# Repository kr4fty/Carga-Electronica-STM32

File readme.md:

# CARGA ELECTRÓNICA FANTASMA

La carga electrónica fantasma es un dispositivo diseñado para simular una carga eléctrica, utilizado principalmente para pruebas y mediciones. 

Este proyecto está basado en un microcontrolador STM32F103, el cual controla la Vgs del MOSFET para regular la corriente.

**Estado del proyecto:** Funcional, pero aún en proceso de creación.

----------------- **BAJO SU RESPONSABILIDAD** ----------------------

### Video

[Demo](https://github.com/user-attachments/assets/e986f7fb-c2cd-4f63-a5ff-34d32783e475)

## Preparación Previa

Dado que cada transistor MOSFET presenta un voltaje umbral de puerta a fuente (Vgs Threshold) único, independientemente del fabricante o del código de identificación, es imperativo llevar a cabo mediciones específicas para determinar este voltaje umbral, así como la relación entre el ciclo de trabajo (Duty Cycle) y la corriente.

Para ello, se empleará el proyecto [Data Logger](https://github.com/kr4fty/DataLogger_STM32) con el fin de registrar estos parámetros. Posteriormente, los valores obtenidos se integrarán en este proyecto para facilitar el control adecuado de nuestra carga electrónica.

## Que incluye este repositorio?

Actualmente este repositorio cuenta con:
 - Diseño del hardware necesario para el proyecto
 - Codigo fuentes, tanto el de Control como la de adquicision de Datos
 - Archivo necesario para simular la placa BluePill, mediante PICSIMLAB

## Materiales

- **Placa:** BLUE PILL (STM32F103)
- **Encoder con botón**
- **Pantalla LCD:** Nokia 5110
- **Buzzer**
- **Sensor de temperatura:** LM35
- **Cooler Fan**
- **Transistor/s MOSFET:** IRFZ44
- **Sensor de corriente:** ACS712-05B

## Principio de Funcionamiento

El MOSFET opera en la zona de saturación (o zona lineal), lo que permite mantener una corriente constante independientemente de la tensión Vds de entrada. Esta característica es ventajosa para nuestra aplicación, ya que al variar la tensión Vgs podemos ajustar la corriente de salida de manera precisa.

La tensión Vds será controlada mediante el STM32F103 utilizando modulación por ancho de pulso (PWM) y un filtro pasa-bajos para obtener una señal de conversión digital a analógica (DAC) de 12 bits.

Debido a la inestabilidad de la potencia con respecto a la temperatura de los mosfset, el lazo de control sera realizado mediante un PID, el cual debera tener en cuenta el rango de temperaturas no solo para mantener la corriente constante, si no tambien para mantener a salvo al dispositivo.

#### Consideraciones importantes de los transistores Mosfet

- **Tensión de umbral (Vgs threshold):** Es el voltaje mínimo que debe aplicarse entre la puerta y la fuente para que el MOSFET comience a conducir corriente entre el drenador y la fuente.
- **Disipación de potencia:** Operar en la zona de saturación genera una significativa disipación de potencia en el MOSFET. Por lo tanto, es necesario implementar un sistema de disipación forzada para evitar el sobrecalentamiento.

#### Modos de Operacion
* Modo de **Corriente Constante**: Este es el modo predeterminado de operación, en el cual el dispositivo mantiene un nivel de corriente constante, determinado por el operador. Este modo es ideal para evaluar el comportamiento de una fuente o batería al operar bajo una corriente estable.
* Modo de **Potencia Constante**: En este modo, el dispositivo ajusta automáticamente la corriente para mantener la potencia consumida constante en la carga. Este enfoque es útil en situaciones donde es crítico mantener un nivel de potencia específico.
* Modo de **Tiempo**: Este modo permite al operador establecer un intervalo de tiempo durante el cual la carga permanecerá activa. Se pueden utilizar cualquiera de los modos anteriores en conjunto con este, según las necesidades de la aplicación.

## Modo de Funcionamiento

 * Al encender el equipo:
  El sistema muestra una pantalla con los siguientes parámetros:
    * **Tensión mínima (Vmin Limite):** 0.00 V (por defecto).
    * **Corriente de carga:** 1.00 A (por defecto).
    * **Modo de Operación:** "Corriente Constante" (por defecto).

 * Modificación de parámetros:
    * **Selección de parámetros:** Gira el encoder para resaltar el parámetro deseado (se invertirán los colores en el seleccionado).
    * **Edición de parámetros:** Realiza un giro rápido hacia la izquierda para entrar en modo edición. El parámetro comenzará a parpadear.
    * **Ajuste de valores:** Gira el encoder para incrementar o decrementar el valor.
    * **Confirmación:** Espera 2 segundos para salir del modo edición.

* Inicio del proceso:
    * **Inicio:** Haz un click corto en el botón para comenzar el proceso.
    * **Parada:** Un click corto detendrá el proceso.

* Modificación de parámetros estando el proceso en funcionamiento:
    - Puedes editar los parámetros de la misma manera que en el estado inicial de arranque (selección y edición).

* Menú:
    * **Acceso al menú:** Haz un doble click en el botón.

    * **Opciones del menú:**
        * Configurar
            * Backlight.
        * Modo de Trabajo
            * Corriente Cte.
            * Potencia Cte.
            * Resistencia Cte.
            * Tiempo Limite
            * Prueba de carga
            * Reset modo actual
        * Set Vmin Limite
        * Calibración
            * Calibrar
            * Ver parámetros
            * Borrar parámetros
        * Reiniciar MCU
        * Salir del Menú

## Hardware

El diseño del hardware se realizó utilizando KiCad, y se ha optimizado para facilitar la conexión de todos los componentes. A continuación, se detallan los aspectos clave del diseño:

### Consideraciones de Diseño

- **Disipación de Calor:** Asegúrate de que el MOSFET esté montado en un disipador de calor adecuado para evitar el sobrecalentamiento durante su operación.
- **Conexiones Seguras:** Verifica que todas las conexiones sean seguras y que no haya cortocircuitos, especialmente en la zona de alimentación.
- **Alimentación:** Utiliza una fuente de alimentación adecuada que pueda proporcionar la corriente necesaria para la carga que se va a simular.

### Imagen del PCB

---

Este documento proporciona una visión general del proyecto y su funcionamiento. Asegúrate de seguir las indicaciones de seguridad al trabajar con componentes electrónicos y realizar pruebas.

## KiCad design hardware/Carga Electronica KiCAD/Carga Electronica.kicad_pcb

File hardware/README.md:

# Hardware

Diseño realizado en KiCAD 8.0.4

## Diagrama electrónico

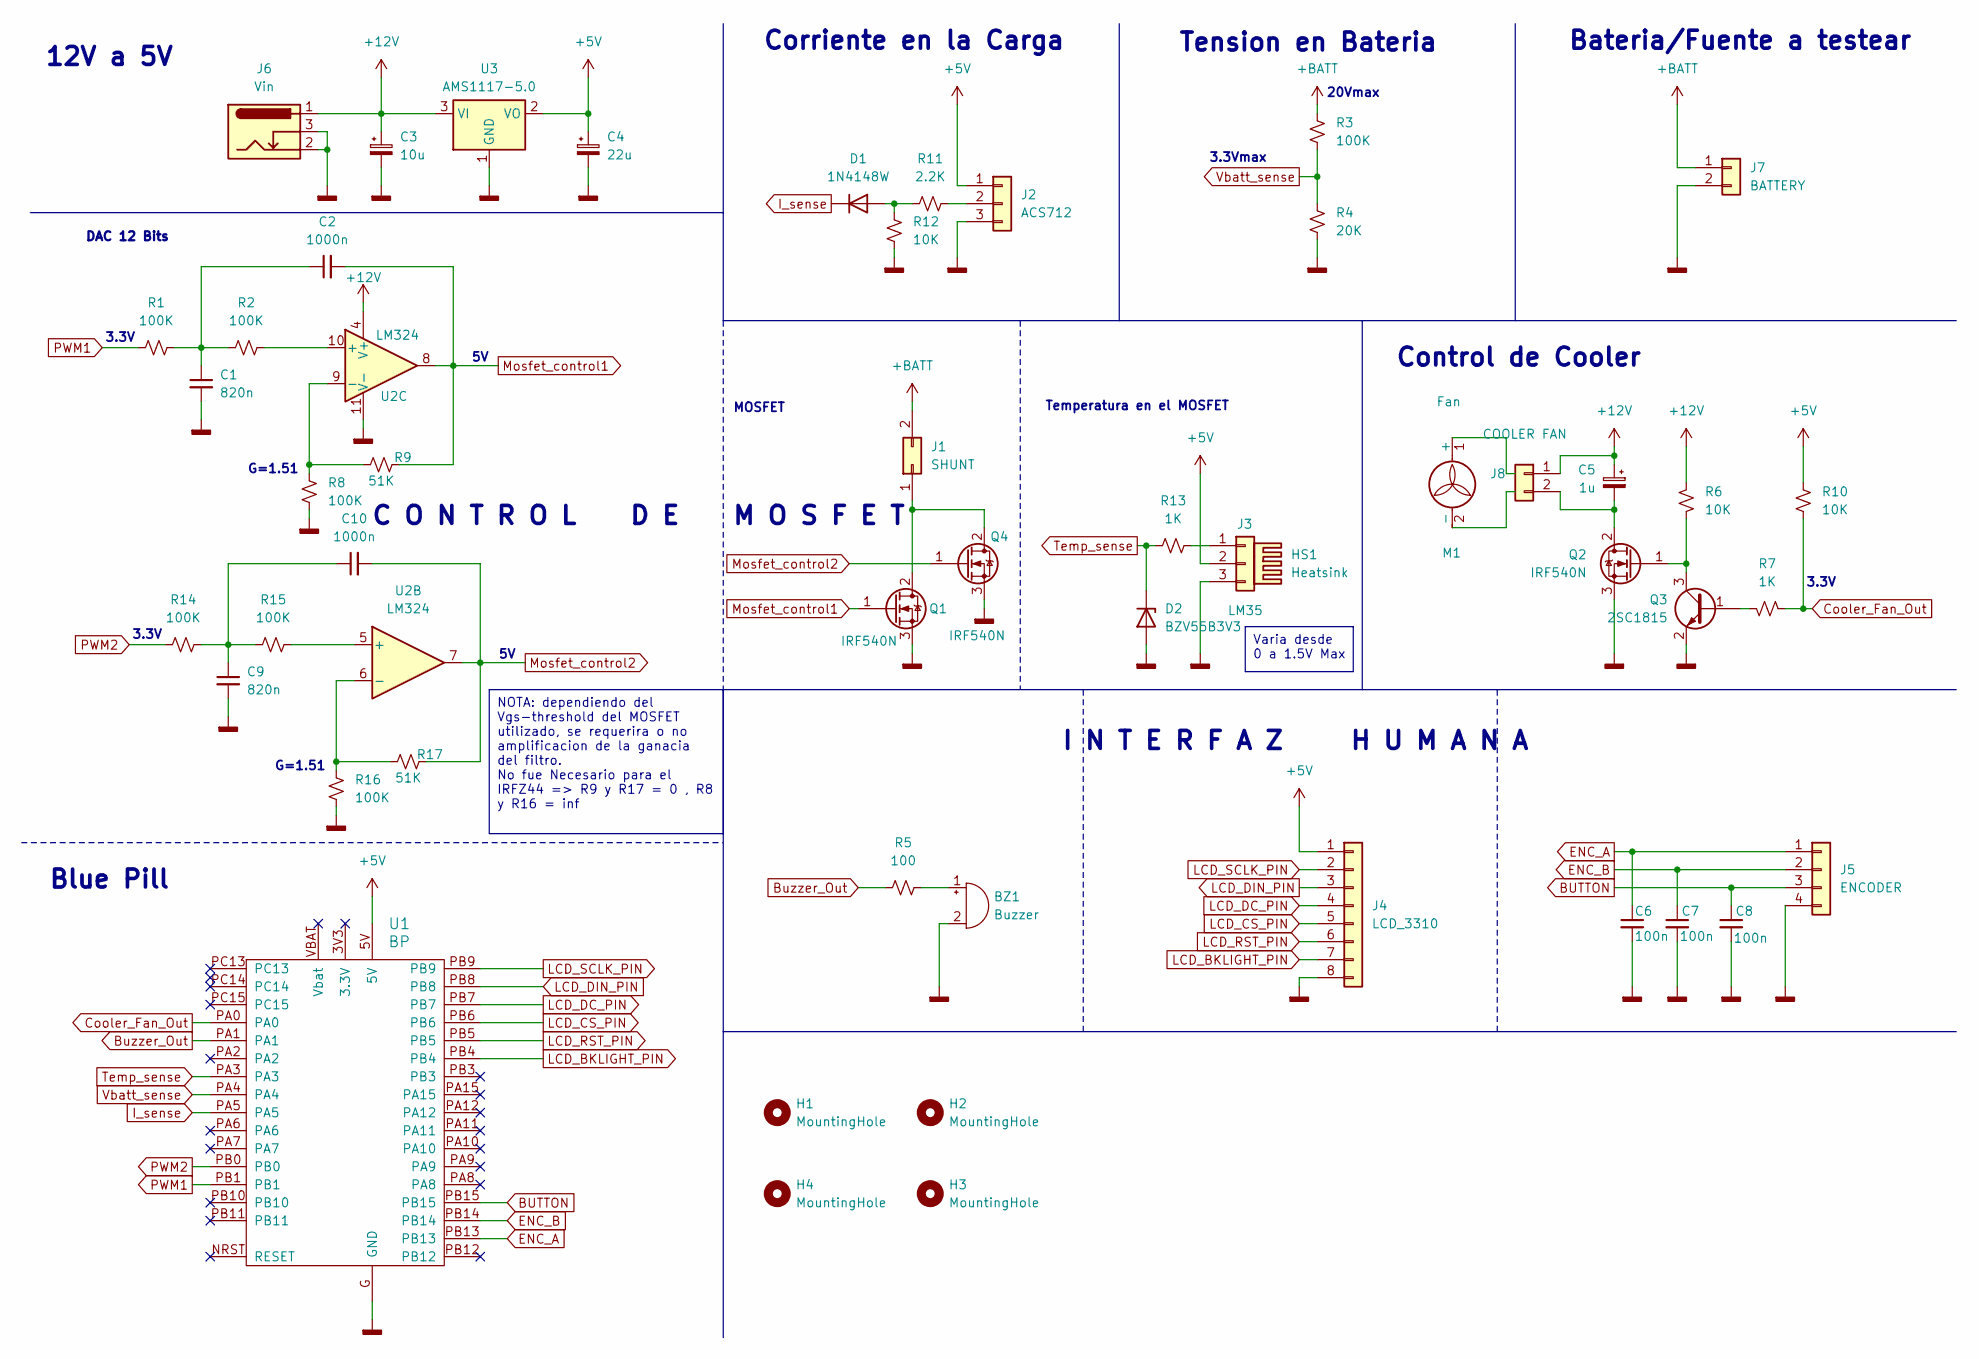
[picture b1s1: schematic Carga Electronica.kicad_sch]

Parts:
BZ1: Buzzer; Buzzer_TDK_PS1240P02BT_D12.2mm_H6.5mm
C1, C9: 820n; C_0805_2012Metric_Pad1.18x1.45mm_HandSolder
C2, C10: 1000n; C_0805_2012Metric_Pad1.18x1.45mm_HandSolder
C3: 10u; CP_Elec_6.3x5.2
C4: 22u; CP_Elec_6.3x5.2
C5: 1u; CP_Elec_6.3x5.2
C6, C7, C8: 100n; C_0805_2012Metric_Pad1.18x1.45mm_HandSolder
D1: 1N4148W; D_SOD-123
D2: BZV55B3V3; D_MiniMELF
H1, H2, H3, H4: MountingHole; MountingHole_2.5mm
HS1: Heatsink
J1: SHUNT; Molex_KK-396_5273-02A_1x02_P3.96mm_Vertical
J2: ACS712; Molex_KK-254_AE-6410-03A_1x03_P2.54mm_Vertical
J3: LM35; Molex_KK-254_AE-6410-03A_1x03_P2.54mm_Vertical
J4: LCD_3310; Molex_KK-254_AE-6410-08A_1x08_P2.54mm_Vertical
J5: ENCODER; Molex_KK-254_AE-6410-04A_1x04_P2.54mm_Vertical
J6: Vin; BarrelJack_Horizontal
J7: BATTERY; Molex_KK-396_5273-02A_1x02_P3.96mm_Vertical
J8: COOLER FAN; Molex_KK-396_5273-02A_1x02_P3.96mm_Vertical
M1: Fan; Molex_KK-254_AE-6410-02A_1x02_P2.54mm_Vertical
Q1, Q4: IRF540N; Molex_KK-396_5273-03A_1x03_P3.96mm_Vertical
Q2: IRF540N; TO-220-3_Vertical
Q3: 2SC1815; SOT-23
R1, R2, R8, R14, R15: 100K; R_0805_2012Metric_Pad1.20x1.40mm_HandSolder
R3, R16: 100K; R_1206_3216Metric_Pad1.30x1.75mm_HandSolder
R4: 20K; R_1206_3216Metric_Pad1.30x1.75mm_HandSolder
R5: 100; R_1206_3216Metric_Pad1.30x1.75mm_HandSolder
R6, R10: 10K; R_1206_3216Metric_Pad1.30x1.75mm_HandSolder
R7: 1K; R_1206_3216Metric_Pad1.30x1.75mm_HandSolder
R9, R17: 51K; R_0805_2012Metric_Pad1.20x1.40mm_HandSolder
R11: 2.2K; R_0805_2012Metric_Pad1.20x1.40mm_HandSolder
R12: 10K; R_0805_2012Metric_Pad1.20x1.40mm_HandSolder
R13: 1K; R_0805_2012Metric_Pad1.20x1.40mm_HandSolder
U1: BP; blue_pill_no_flashing_port
U2: LM324; SOIC-14_3.9x8.7mm_P1.27mm
U3: AMS1117-5.0; SOT-223-3_TabPin2

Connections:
+5V: C4.1, J2.1, J3.2, J4.1, R10.1, U1.5V, U3.2 (VO)
+12V: C3.1, C5.1, J6.1, J8.1, R6.1, U2.4 (V+), U3.3 (VI)
+BATT: J1.2, J7.1, R3.1
BUTTON: C8.1, J5.3, U1.PB15
Buzzer_Out: R5.1, U1.PA1
Cooler_Fan_Out: R7.2, R10.2, U1.PA0
ENC_A: C6.1, J5.1, U1.PB13
ENC_B: C7.1, J5.2, U1.PB14
GNDD: BZ1.2 (-), C1.2, C3.2, C4.2, C6.2, C7.2, C8.2, C9.2, D2.2 (A), J2.3, J3.3, J4.8, J5.4, J6.2, J6.3, J7.2, Q1.3 (S), Q2.3 (S), Q3.2 (E), Q4.3 (S), R4.2, R8.2, R12.2, R16.2, U1.G (GND), U2.11 (V-), U3.1 (GND)
I_sense: D1.1 (K), U1.PA5
LCD_BKLIGHT_PIN: J4.7, U1.PB4
LCD_CS_PIN: J4.5, U1.PB6
LCD_DC_PIN: J4.4, U1.PB7
LCD_DIN_PIN: J4.3, U1.PB8
LCD_RST_PIN: J4.6, U1.PB5
LCD_SCLK_PIN: J4.2, U1.PB9
Mosfet_control1: C2.2, Q1.1 (G), R9.2, U2.8
Mosfet_control2: C10.2, Q4.1 (G), R17.2, U2.7
unnamed: BZ1.1 (+), R5.2
unnamed: C1.1, C2.1, R1.2, R2.1
unnamed: C9.1, C10.1, R14.2, R15.1
unnamed: D1.2 (A), R11.1, R12.1
unnamed: J1.1, Q1.2 (D), Q4.2 (D)
unnamed: J2.2, R11.2
unnamed: J3.1, R13.2
unnamed: C5.2, J8.2, Q2.2 (D)
unnamed: Q2.1 (G), Q3.3 (C), R6.2
unnamed: Q3.1 (B), R7.1
unnamed: R15.2, U2.5 (+)
unnamed: R16.1, R17.1, U2.6 (-)
unnamed: R2.2, U2.10 (+)
unnamed: R8.1, R9.1, U2.9 (-)
PWM1: R1.1, U1.PB1
PWM2: R14.1, U1.PB0
Temp_sense: D2.1 (K), R13.1, U1.PA3
Vbatt_sense: R3.2, R4.1, U1.PA4

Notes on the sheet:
NOTA: dependiendo del Vgs-threshold del MOSFET utilizado, se requerira o no amplificacion de la ganacia del filtro. No fue Necesario para el IRFZ44 => R9 y R17 = 0 , R8 y R16 = inf
Varia desde 0 a 1.5V Max
C O N T R O L D E M O S F E T
Corriente en la Carga
G=1.51
3.3V
MOSFET
Control de Cooler
DAC 12 Bits
Temperatura en el MOSFET
3.3Vmax
Tension en Bateria
Blue Pill
I N T E R F A Z H U M A N A
12V a 5V
20Vmax
Bateria/Fuente a testear

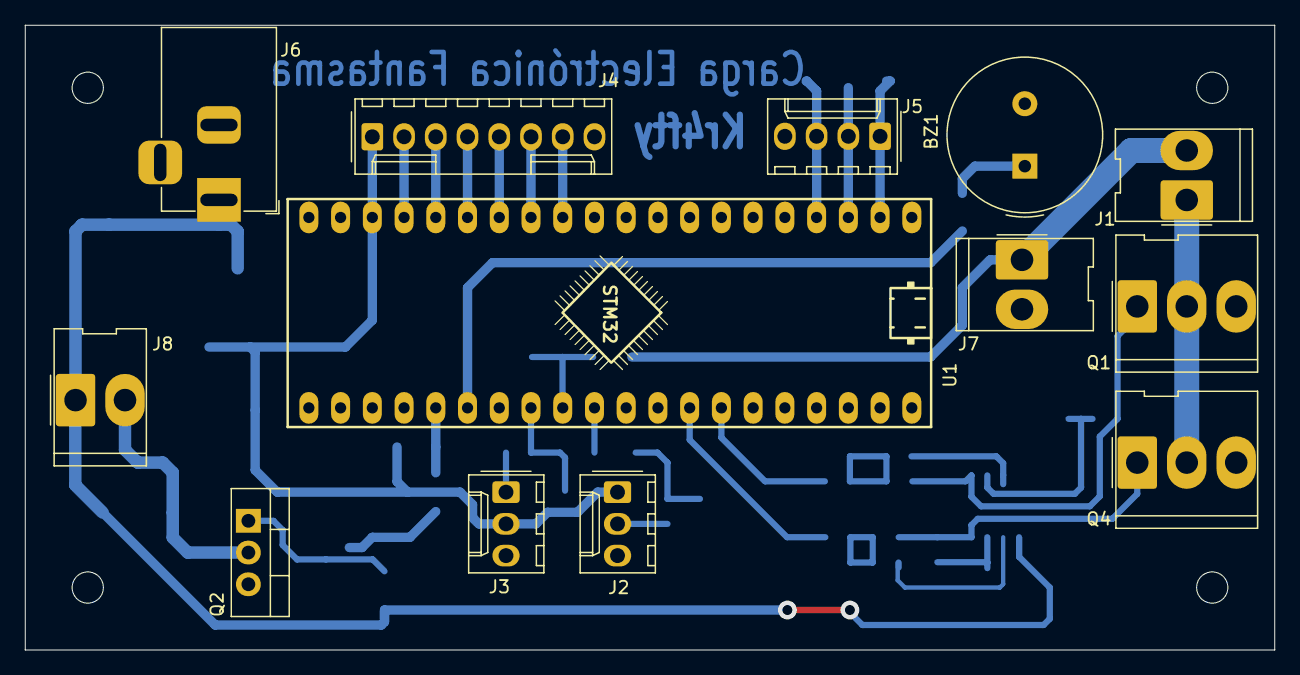
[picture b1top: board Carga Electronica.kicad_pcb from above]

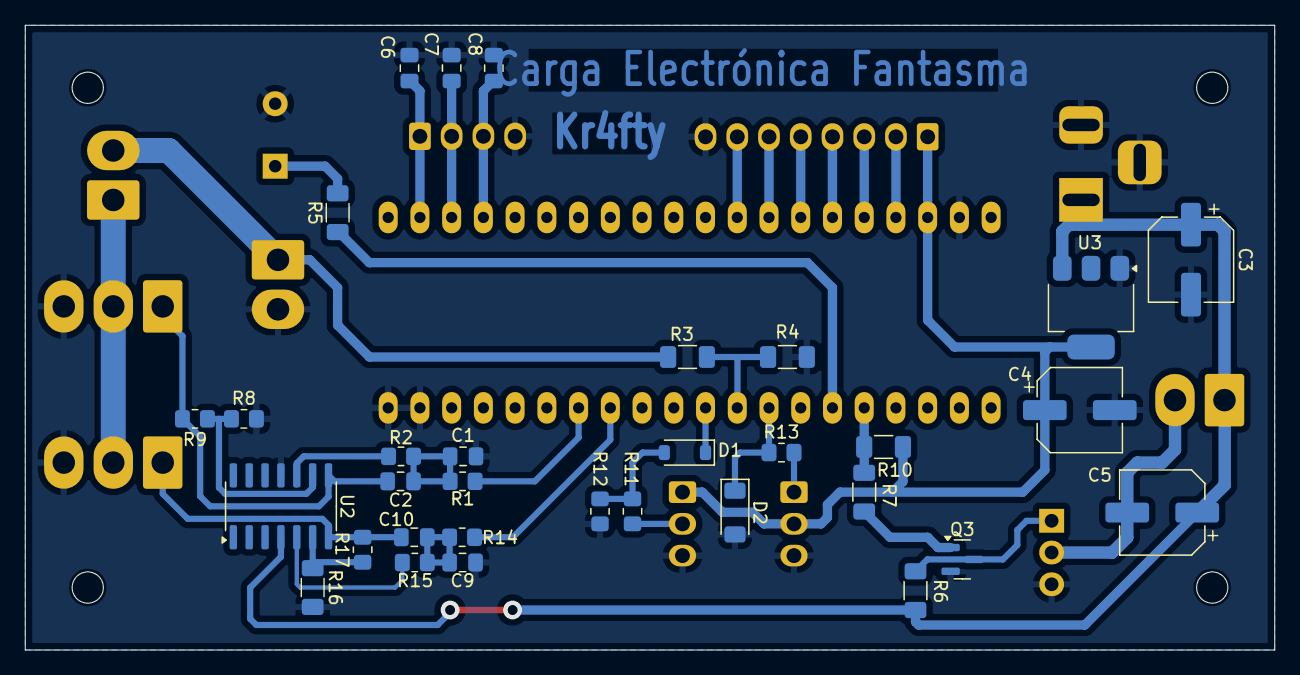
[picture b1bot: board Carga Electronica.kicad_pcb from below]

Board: 2 copper layers, 100.0 x 50.0 mm, 49 parts (32 on the bottom side), 36 nets.

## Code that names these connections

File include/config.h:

/*
 *                      BLUE PILL PINOUT
 *
 *                  ,----------------------,
 *                  |o|PB12 | USB |   GND|o|          
 *   ENCODER_PIN_A  |o|PB13 '-----'   GND|o|  
 *   ENCODER_PIN_B  |o|PB14          3.3v|o|  
 *      BUTTON_PIN  |o|PB15          NRST|o|
 *                  |o|PA8           PB11|o|
 *                  |o|PA9           PB10|o|  
 *                  |o|PA10           PB1|o|  PWM_PIN [PWM_PIN1]
 *                  |o|PA11           PB0|o|  [PWM_PIN2]
 *                  |o|PA12           PA7|o|  
 *                  |o|PA15    /\     PA6|o|  
 *                  |o|PB3    /  \    PA5|o|  IBATT_SENSE_PIN
 * LCD_BKLIGHT_PIN  |o|PB4    \  /    PA4|o|  VBATT_SENSE_PIN
 *     LCD_RST_PIN  |o|PB5     \/     PA3|o|  FET_TEMP_SENSE_PIN
 *      LCD_CS_PIN  |o|PB6            PA2|o|
 *      LCD_DC_PIN  |o|PB7  =======   PA1|o|  BUZZER_PIN
 *     LCD_DIN_PIN  |o|PB8  =======   PA0|o|  COOLER_FAN_PIN
 *    LCD_SCLK_PIN  |o|PB9           PC15|o|
 *                  |o|5V            PC14|o|
 *                  |o|GND  . . . .  PC13|o|
 *                  |o|3.3V =======  VBAT|o|
 *                  '_'_____|_|_|_|______'_'
 *                          | | | |
 * 
 * 
 * 
 */



#ifndef _CONFIG_H
#define _CONFIG_H

// LED BUILTIN
#define LED         LED_BUILTIN // PC13

// LCD
#define LCD_SCLK_PIN        PB9
#define LCD_DIN_PIN         PB8
#define LCD_DC_PIN          PB7
#define LCD_CS_PIN          PB6
#define LCD_RST_PIN         PB5
#define LCD_BKLIGHT_PIN     PB4

// ENCODER and BUTTTON
#define ENCODER_PIN_A      PB13
#define ENCODER_PIN_B      PB14
#define BUTTON_PIN         PB15
#define ENCODER_VCC_PIN      -1 // Uso VCC de la placa
#define ENCODER_STEPS         4
#define ENCODER_CENTRAL_PIN_TO_VCC false // se usa pin central conectado a GND

// BUZZER
#define BUZZER_PIN          PA1 // Canal 2 de TIM2

// COOLER FAN
#define COOLER_FAN_PIN      PA0

//MOSFET TEMPERATURE
#define FET_TEMP_SENSE_PIN  PA3
#define FET_MAX_TEMP        100 //ºC máximos
#define FET_MIN_TEMP         30 //ºC mínimo para encender el cooler

// PWM
#define PWM1_PIN            PB1 // Canal 4 de TIM3
#define PWM2_PIN            PB0 // Canal 3 de TIM3

//#define FREQUENCY         10000 // 10KHz
#define PWM_INITIAL_DUTY      0 // 0%
#define PWM__RESOLUTION    4095 // Resolución de 12 bits

// VBATT IBATT
#define VBATT_SENSE_PIN     PA4
#define IBATT_SENSE_PIN     PA5

//PID
#define RESOLUTION PWM_RESOLUTION

// MODO DEPURACIÓN
/*  Para gráficar la respuesta con los parámetros PID seleccionados
 *  Utilizar la aplicación, en la PC, serial_port_plotter
 */
//#define DEBUG // Descomente esta linea para habilitar

#endif

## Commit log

2024-08-30 nuevo repositorio
2024-08-30 quitar lo innecesario
2024-08-31 .gitignore is now working
2024-09-04 Sensado y calculo de V e I de carga
2024-09-04 Primer testeo de la Carga, funcional
2024-09-05 Prueba de implementar PID
2024-09-06 Primera implementacion funcional del PID
2024-09-09 Mejoras en el algoritmo de calculo para mediciones de V e I
2024-09-09 Implementacion del calculo para Wh y Ah
2024-09-09 Imprimir en el LCD unicamente lo que se actualizo
2024-09-09 Cambios menores
2024-09-09 Se agrega proyecto en KiCAD del Hardware utilizado
2024-09-09 fix al crear enlaces a archivos
2024-09-10 Implementacion de doble salida PWM
2024-09-10 Muestra el Setpoint cuando no esta funcionando
2024-09-10 Implementacion funcional de doble mosfet
2024-09-10 reimplementacion de floatTostr()
2024-09-10 Quitando codigo viejo
2024-09-11 Teniendo en cuenta Vgs_threshold. Valor particular de cada MOSFET
2024-09-11 Chequeo continuo de la Tension de entrada de Bateria/Fuente
2024-09-11 se agrega reseteo de contadores mediante pulsacion larga
2024-09-12 testeo de tension de entrada y prioridad en la notificaciones
2024-09-13 modificacion del sistema de notificaciones
2024-09-13 reordeno la impresion de temperatura
2024-09-13 notificaciones por exceso de temperatura
2024-09-13 se agregan mini notificaciones
2024-09-13 Repositorio hecho publico
2024-09-15 readme.md
2024-09-15 mala edicion de readme.md
2024-09-18 acomodando variables
2024-09-20 correccion de readme.md
2024-09-20 add DataLogger repository
2024-10-02 resolviendo problemas del algoritmo de control PID
2024-10-02 se agrega modo graficar "respuesta al step"
2024-10-02 acomodando el algoritmo del boton
2024-10-02 fix Modo Calibracion
2024-10-02 Se cambio el divisor resistivo por R de precision
2024-10-03 fix sobreimpulso al volver a conectar la bateria con la carga activada
2024-10-07 fix notificacion cuando se desconecta bateria en funcionamiento y se apaga la carga
2024-10-09 se agrega nuevo entorno para emular mediante PICSIMLAB
2024-10-09 fix mensaje de "no battery" cuando se decsconectaba la bateria y se variaba el Setpoint
2024-10-09 deteccion de pulsacion, se actua solo si se detecta un valor True
2024-10-10 solo estando encendida se muestra el reloj con colores invertidos
2024-10-10 se agregan Macros en display.h
2024-10-10 organizando codigo para mejor legibilidad
2024-10-13 se agrega deteccion de doble click rapido del boton para futuros usos
2024-10-13 se agragan archivos de simulacion para PICSIMLAB
2024-10-13 readme.md dentro de `simulacion`
2024-10-14 retoques en 'encoder.h'
2024-10-14 optimizado `encoder.h`
2024-10-15 se agrega soporte para menus, se inicia con un doble click
2024-10-16 reorganizando funciones de encoder.h y display.h dentro de menu.h
2024-10-16 mejoras en el resaltado de un Item seleccionado en el menu
2024-10-17 se agrega acciones para los parametros de calibracion de I
2024-10-18 reacomodando sector menus
2024-10-18 se intento implementar MODOS, por ahora con problemas en la impresion de mediciones
2024-10-21 modo P CTE funcionando
2024-10-22 reorganizando el codigo
2024-10-23 modo TIEMPO activado y funcionando
2024-10-23 se modifica la forma que se muestra al cargar el Periodo de Tiempo
2024-10-23 ahora se muestra el tiempo en decremento en MODO TIEMPO
2024-10-23 eliminando variables duplicadas en `tclock.h`
2024-10-23 se agregan `modos` a readme.md
2024-10-23 readme.md del hardware
2024-10-24 se agrega seleccion de modo en funcion `Tiempo`
2024-10-24 se agrega video de demostracion en readme.md
    usando PICSIMLAB para emular la placa de control
2024-10-24 acomodando las variables globales y locales
2024-10-24 fix al reiniciar los contadores, totalTime debe tomar un valor dependiendo del modo seleccionado
2024-10-24 se establece identacion de 4 espacion en los archivos que tenian 2 espacios
2024-10-24 cambio delay por click para cerrar el mensaje
2024-10-24 se agrega mensaje "click -> salir" cuando se muestra mensaje de información
2024-10-25 se agrega modo Resistencia Constante
2024-10-25 fix modo R constante, ahora en funcionamiento
2024-10-25 fix variables de tiempo no tomaban los valores correctos al cambiar de modo
2024-10-25 detener las salidas pwm si entro al submenu `Tiempo`
2024-10-25 renicio de contadores cuando se cambia de modo de operacion
2024-10-25 todos los modos de trabajo funcionando
2024-10-26 se cambia la presentacion del menu
2024-10-29 se agrega modo ´Prueba de Carga`
2025-01-04 Cambio en la escala para I < 1A
2025-02-12 Interrupcio de notificacion de No Battery dentro del Menu
2025-02-12 fix notificaciones al estar Menu activo
2025-02-14 se implemento el guardado de parametros de calibracion en la EEPROM
2025-02-19 evitar arranque involuntario en modo Calibracion en el arranque
2025-02-19 se agrega configuracion inicial de Vmin de corte y Corriente de la Carga
2025-02-20 modificación en la selección de Vmin
2025-02-20 se agrega Parpadeo del parámetro seleccionado
2025-02-20 al arrancar de forma directa, solo un click corto, no se seteaba correctamente la corriente de carga
2025-02-24 al iniciar, para comenzar a configurar un parámetro se deberá girar hacia la izquierda sobre el deseado y luego un click para guardar
2025-02-25 se mejora la configuración y arranque inicial. Solo se modificara el parámetro si se hace un giro izquierdo rápido
2025-02-26 se modifica la forma de selección del Modo de Control, en modo Timer
2025-02-26 se actualizo el video demo
2025-03-03 fix, no se podía cambiar de menu Item cuando se esta en modo _Prueba de Carga_
2025-03-03 sin cambios en el código, solo ortografía
2025-03-05 reorganización del Menú
2025-03-05 se agrego la opción Reset al Menú
2025-03-11 mejoras en la interfaz humana
2025-03-12 fix, no se mostraba el resumen de valores medidos cuando se detenía el proceso
2025-03-13 fix, en modo Rcte y Pcte, arrancaba con valores por defecto incorrectos
2025-03-14 fix, tras salir del menu no se actualizaba correctamente la configuración del encoder y la impresión del tiempo
2025-03-17 refresco de pantalla cada 20mesg
2025-03-17 fix, si cambiaba de modo de trabajo, estando el anterior en funcionamiento, el proceso no se reiniciaba/apagaba
